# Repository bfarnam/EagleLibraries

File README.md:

# EagleLibraries
A collection of some personal EAGLE CAD Libraries.. always a work in progress.

Use them as you see fit.  And of course if you make any meaningful additions, I am always happy to include them.

Created with Eagle Version 7.7.0

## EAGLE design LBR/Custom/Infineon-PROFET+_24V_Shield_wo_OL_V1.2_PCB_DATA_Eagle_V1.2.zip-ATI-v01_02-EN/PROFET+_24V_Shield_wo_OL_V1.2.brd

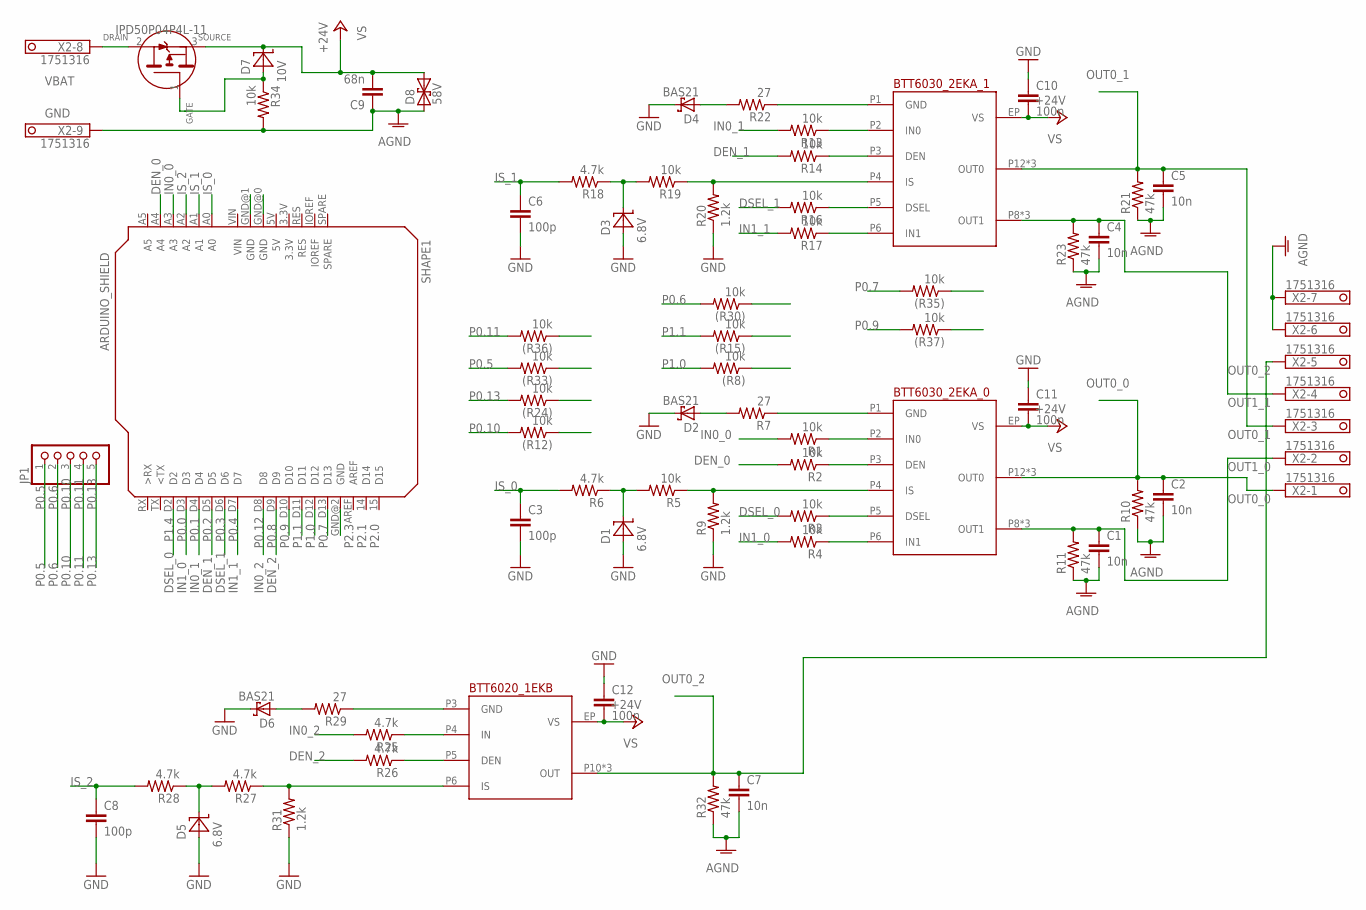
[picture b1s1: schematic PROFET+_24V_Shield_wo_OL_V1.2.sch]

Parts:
(R8), (R12), (R15), (R24), (R30), (R33), (R35), (R36), (R37): 10k; 0603-RES
BTT6020_1EKB: INFINEON_BTS5008-1EKB_2; IFX_PG_DSO_14_47_EP
BTT6030_2EKA_0, BTT6030_2EKA_1: INFINEON_BTS5020-2EKA; IFX_PG_DSO_14_40_EP
C1, C2, C4, C5, C7: 10n; 0603-CAP
C3, C6, C8: 100p; 0603-CAP
C9: 68n; 0603-CAP
C10, C11, C12: 100n; 0603-CAP
D1, D3, D5: 6.8V; SMD-PACKAGES_SOD80
D2, D4, D6: BAS21; SOT23
D7: 10V; SMD-PACKAGES_SOD80
D8: 58V; SMA
IPD50P04P4L: INF-PG-TO252-3-313_L_1; INF-PG-TO252-3-313_L_1PRIMARY
JP1: PINHD-1X5; 1X05
R1, R2, R3, R4, R5, R13, R14, R16, R17, R19, R34: 10k; 0603-RES
R6, R18, R25, R26, R27, R28: 4.7k; 0603-RES
R7, R22, R29: 27; 0603-RES
R9, R20, R31: 1.2k; R1206
R10, R11, R21, R23, R32: 47k; 0603-RES
SHAPE1: ARDUINO_SHIELD; XMC1100_FOR_ARDUINO
X2: 1751316

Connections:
DEN_0: R2.2, SHAPE1.A4
DEN_1: R14.2, SHAPE1.D5
DEN_2: R26.2, SHAPE1.D9
DSEL_0: R3.2, SHAPE1.D2
DSEL_1: R16.2, SHAPE1.D6
GND: C1.2, C2.2, C3.2, C4.2, C5.2, C6.2, C7.2, C8.2, C9.1, C10.1, C11.1, C12.1, D1.A, D2.3 (C), D3.A, D4.3 (C), D5.A, D6.3 (C), D8.A (1), R9.1, R10.1, R11.1, R20.1, R21.1, R23.1, R31.1, R32.1, R34.2, SHAPE1.GND@0 (GND), SHAPE1.GND@1 (GND), SHAPE1.GND@2 (GND), X2.6, X2.7, X2.9
IN0_0: R1.2, SHAPE1.A3
IN0_1: R13.2, SHAPE1.D4
IN0_2: R25.2, SHAPE1.D8
IN1_0: R4.2, SHAPE1.D3
IN1_1: R17.2, SHAPE1.D7
IS_0: C3.1, R6.2, SHAPE1.A0
IS_1: C6.1, R18.2, SHAPE1.A1
IS_2: C8.1, R28.2, SHAPE1.A2
unnamed: BTT6030_2EKA_1.P5 (DSEL), R16.1
unnamed: D7.A, IPD50P04P4L.1 (GATE_PIN1), R34.1
unnamed: BTT6030_2EKA_1.P6 (IN1), R17.1
unnamed: BTT6030_2EKA_1.P3 (DEN), R14.1
unnamed: D2.1 (A), R7.2
unnamed: BTT6030_2EKA_1.P2 (IN0), R13.1
unnamed: BTT6030_2EKA_1.P1 (GND), R22.1
unnamed: BTT6030_2EKA_1.P4 (IS), R19.1, R20.2
unnamed: D4.1 (A), R22.2
unnamed: D3.K (C), R18.1, R19.2
unnamed: BTT6030_2EKA_0.P5 (DSEL), R3.1
unnamed: BTT6030_2EKA_0.P6 (IN1), R4.1
unnamed: BTT6030_2EKA_0.P3 (DEN), R2.1
unnamed: BTT6030_2EKA_0.P2 (IN0), R1.1
unnamed: BTT6030_2EKA_0.P1 (GND), R7.1
unnamed: BTT6030_2EKA_0.P4 (IS), R5.1, R9.2
unnamed: D1.K (C), R5.2, R6.1
unnamed: BTT6020_1EKB.P5 (DEN), R26.1
unnamed: BTT6020_1EKB.P4 (IN), R25.1
unnamed: BTT6020_1EKB.P3 (GND), R29.1
unnamed: BTT6020_1EKB.P6 (IS), R27.1, R31.2
unnamed: D6.1 (A), R29.2
unnamed: D5.K (C), R27.2, R28.1
OUT0_0: BTT6030_2EKA_0.P12 (OUT0), BTT6030_2EKA_0.P13 (OUT0), BTT6030_2EKA_0.P14 (OUT0), C2.1, R10.2, X2.1
OUT0_1: BTT6030_2EKA_1.P12 (OUT0), BTT6030_2EKA_1.P13 (OUT0), BTT6030_2EKA_1.P14 (OUT0), C5.1, R21.2, X2.3
OUT0_2: BTT6020_1EKB.P10 (OUT), BTT6020_1EKB.P11 (OUT), BTT6020_1EKB.P12 (OUT), C7.1, R32.2, X2.5
OUT1_0: BTT6030_2EKA_0.P8 (OUT1), BTT6030_2EKA_0.P9 (OUT1), BTT6030_2EKA_0.P10 (OUT1), C1.1, R11.2, X2.2
OUT1_1: BTT6030_2EKA_1.P8 (OUT1), BTT6030_2EKA_1.P9 (OUT1), BTT6030_2EKA_1.P10 (OUT1), C4.1, R23.2, X2.4
P0.5: (R33).2, JP1.1
P0.6: (R30).2, JP1.2
P0.7: (R35).2, SHAPE1.D13
P0.9: (R37).2, SHAPE1.D10
P0.10: (R12).2, JP1.3
P0.11: (R36).2, JP1.4
P0.13: (R24).2, JP1.5
P1.0: (R8).2, SHAPE1.D12
P1.1: (R15).2, SHAPE1.D11
VBAT: IPD50P04P4L.2 (DRAIN_PIN2), X2.8
VS: BTT6020_1EKB.EP (VS), BTT6030_2EKA_0.EP (VS), BTT6030_2EKA_1.EP (VS), C9.2, C10.2, C11.2, C12.2, D7.K (C), D8.C (2), IPD50P04P4L.3 (SOURCE_PIN3)

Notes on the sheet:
P0.5
P0.6
P0.10
P0.11
P0.13
P0.0
P0.1
P0.2
P0.3
P0.4
P0.8
P0.9
P1.4
P0.7
P0.12
P1.0
P1.1
P2.0
P2.1
P2.3

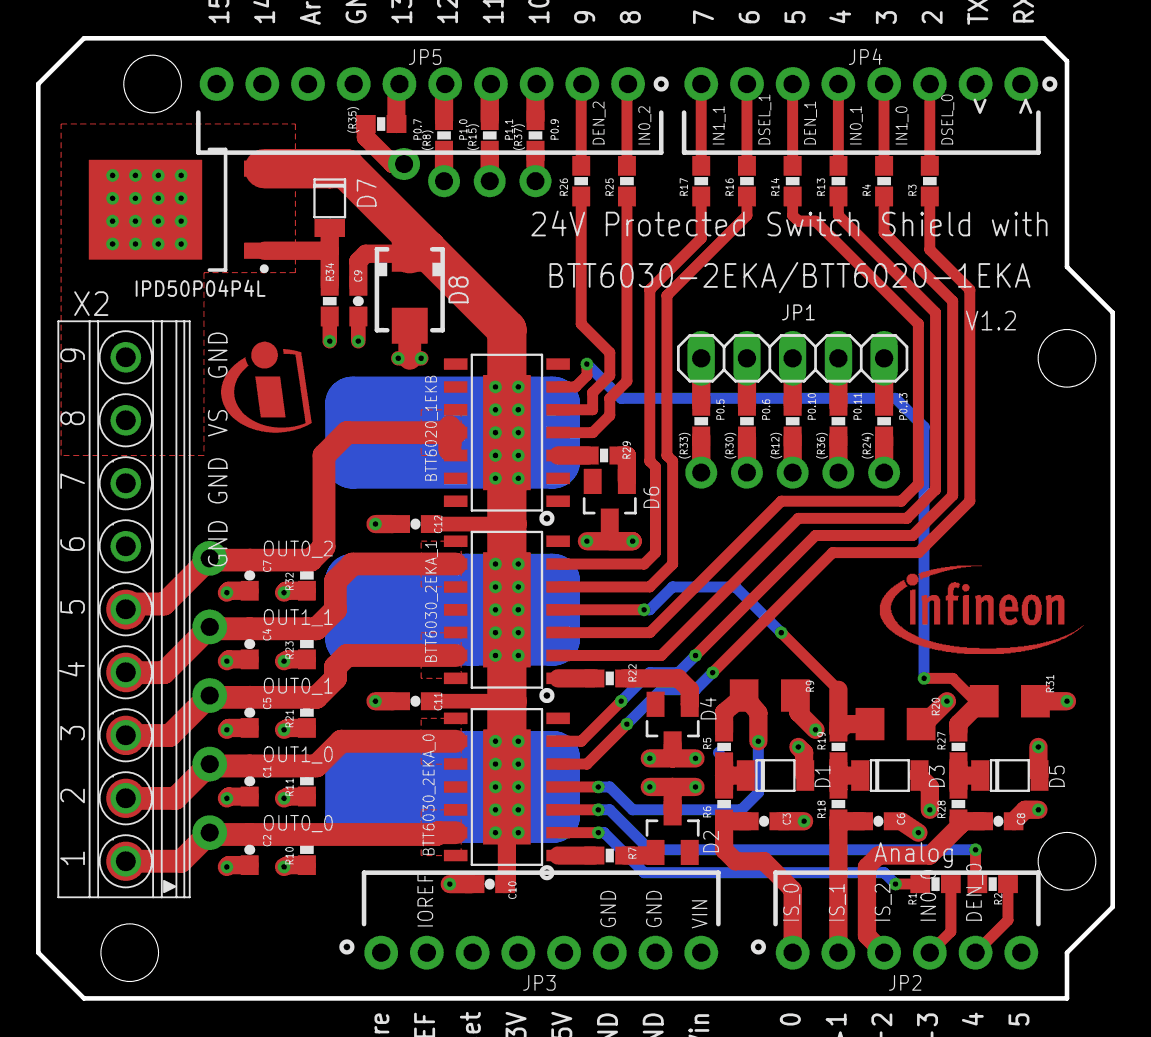
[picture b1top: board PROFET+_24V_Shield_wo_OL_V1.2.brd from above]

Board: 2 copper layers, 59.7 x 53.3 mm, 66 parts (0 on the bottom side), 53 nets.

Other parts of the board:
U$3: INFINEON_LOGO_5
U$6: INFINEON_ICON_5

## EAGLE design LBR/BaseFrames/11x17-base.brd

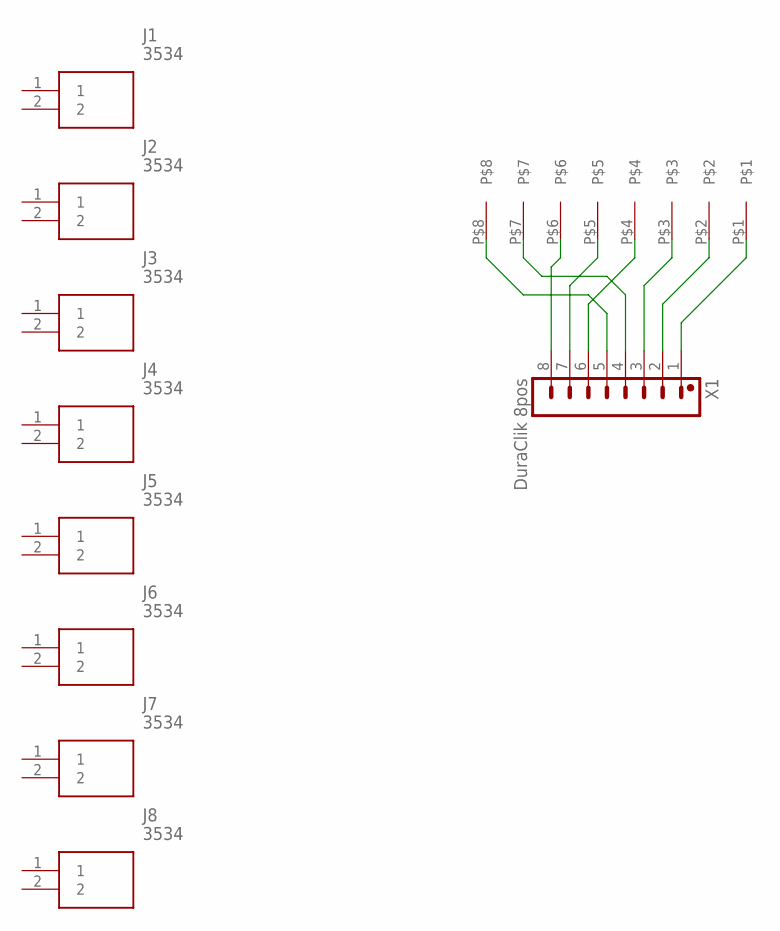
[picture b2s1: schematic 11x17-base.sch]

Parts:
J1, J2, J3, J4, J5, J6, J7, J8: 3534
U$2: YB2; YB2___K_01
X1: DuraClik 8pos; 560020-08

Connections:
unnamed: U$2.P$3, X1.3
unnamed: U$2.P$2, X1.2
unnamed: U$2.P$1, X1.1
unnamed: U$2.P$7, X1.4
unnamed: U$2.P$8, X1.5
unnamed: U$2.P$4, X1.6
unnamed: U$2.P$5, X1.7
unnamed: U$2.P$6, X1.8

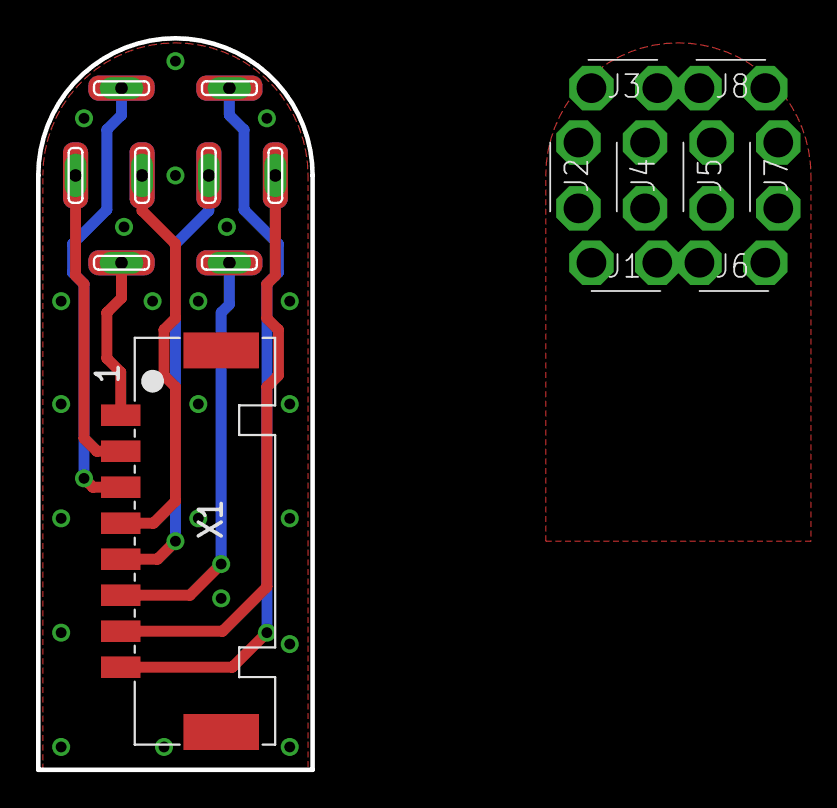
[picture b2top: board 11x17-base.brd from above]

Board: 2 copper layers, 15.2 x 40.6 mm, 11 parts (0 on the bottom side), 8 nets.

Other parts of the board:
U$1: FRAME_B_L

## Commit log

2022-05-22 added libraries
2022-06-19 added crystal
2022-06-29 added parts
2022-07-04 lib updates
2022-07-07 added 3.3v
2022-07-11 added my custom eagle.scr for grids
2022-07-11 added my eaglerc.usr
2022-07-12 lib and pcb updates
2022-07-18 lib and sch updates, added spice
2022-07-20 fixed some packages
2022-07-21 updated foot prints
2022-07-25 updated footprints
2022-07-29 update profets
2022-08-21 update libs
2022-10-04 updated devices
2022-12-15 lib changes
2023-09-08 add new parts
2023-11-05 New Dev
2023-11-12 updated components
2024-11-05 layer changes
2025-03-08 started lbr consolidations
2025-03-08 reorganize
2025-03-08 adds
2025-03-10 added files
2025-03-10 organizing
2025-03-10 organize
2025-03-10 updates to schematic
2025-03-11 organization
2025-03-13 organize libs
2025-03-15 moving 3d objects
2025-03-21 part add
2025-03-29 housekeeping
2025-04-13 new parts
2025-04-19 updates to dru and cam

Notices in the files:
LBR/BaseFrames/11x17-base.brd:
COPYRIGHT: Copyright (C) 2023 All Rights Reserved
